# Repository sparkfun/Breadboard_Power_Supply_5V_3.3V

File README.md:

SparkFun Breadboard Power Supply 5V/3.3V
========================================

[*SparkFun Breadboard Power Supply 5V/3.3V (PRT-00114)*](https://www.sparkfun.com/products/114)

ere is a very simple breadboard power supply kit that takes power from a DC wall wart and outputs a selectable 5V or 3.3V regulated voltage.

Repository Contents
-------------------

* **/Hardware** - Eagle design files (.brd, .sch)
* **/Production** - Production panel files (.brd)

Documentation
--------------
* **[Hookup Guide](https://www.sparkfun.com/tutorials/297)** - Basic hookup guide for the Breadboard Power Supply.
* **[SparkFun Fritzing repo](https://github.com/sparkfun/Fritzing_Parts)** - Fritzing diagrams for SparkFun products.
* **[SparkFun 3D Model repo](https://github.com/sparkfun/3D_Models)** - 3D models of SparkFun products. 

License Information
-------------------
This product is _**open source**_! 

The **hardware** is released under [Creative Commons ShareAlike 4.0 International](https://creativecommons.org/licenses/by-sa/4.0/).

Please use, reuse, and modify these files as you see fit. Please maintain attribution to SparkFun Electronics and release anything derivative under the same license.

Distributed as-is; no warranty is given.

- Your friends at SparkFun.

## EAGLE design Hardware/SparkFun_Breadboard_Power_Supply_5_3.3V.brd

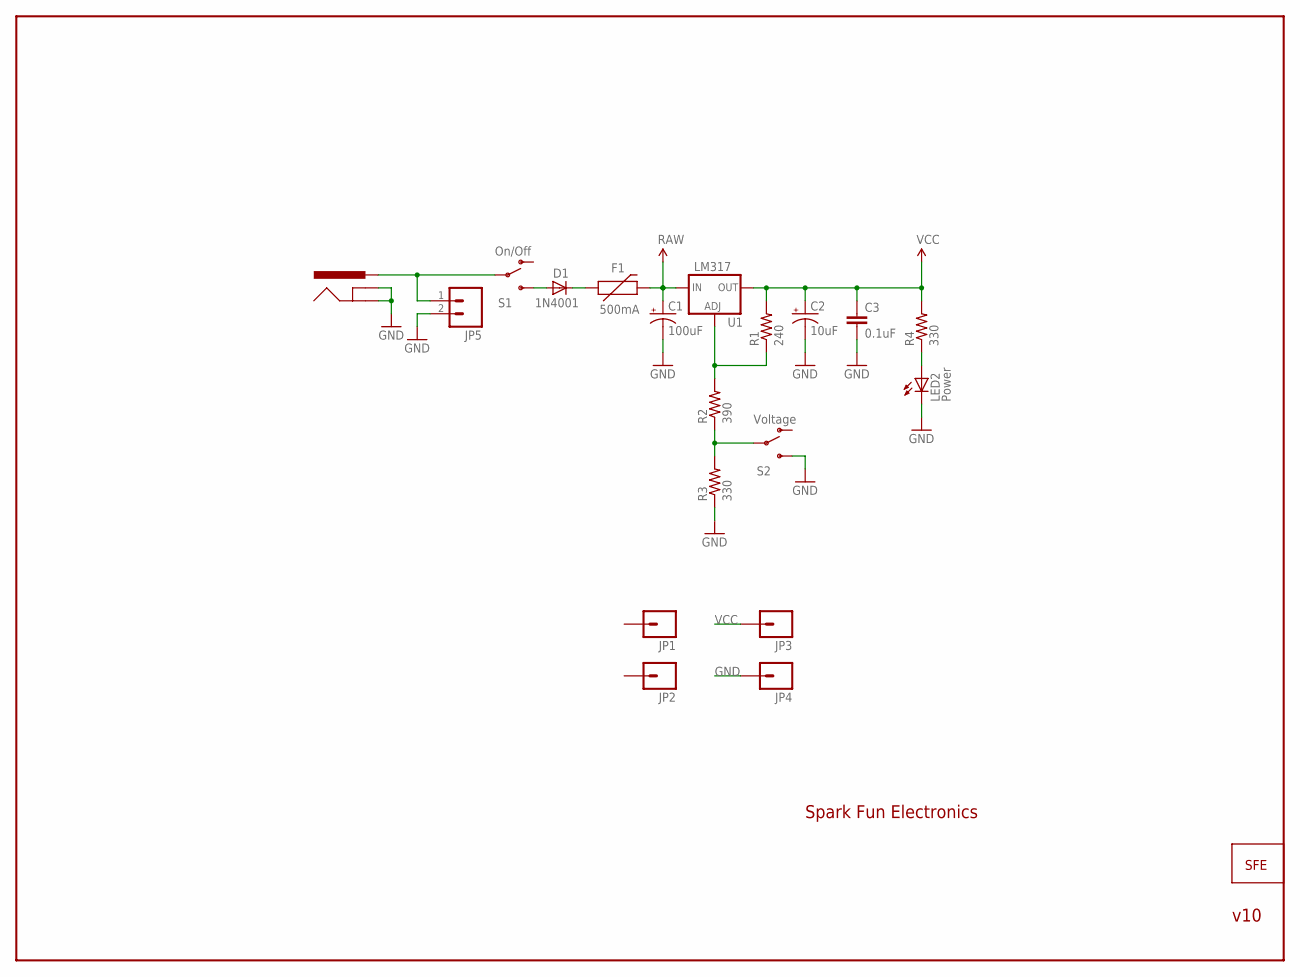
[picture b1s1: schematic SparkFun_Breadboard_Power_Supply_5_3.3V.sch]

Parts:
C1: 100uF; CPOL-RADIAL-100UF-25V
C2: 10uF; CPOL-RADIAL-10UF-25V
C3: 0.1uF; CAP-PTH-SMALL2
D1: 1N4001; DIODE-0.4
F1: 500mA; PTC
J1: POWER_JACKPTH; POWER_JACK_PTH
JP1, JP2, JP3, JP4: M01PTH; 1X01
JP5: M02PTH; 1X02
LED2: Power; LED5MM
R1: 240; AXIAL-0.3
R2: 390; AXIAL-0.3
R3, R4: 330; AXIAL-0.3
S1: On/Off; SWITCH-SPST
S2: Voltage; SWITCH-SPST
U1: LM317; TO220-ADJ
U$1: LOGO-SFESK; SFE-LOGO-FLAME

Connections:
GND: C1.2 (-), C2.2 (-), C3.2, J1.GND, J1.GNDBREAK, JP4.1, JP5.2, LED2.K (C), R3.P$1 (1), S2.3 (S)
unnamed: D1.C, F1.P$1 (1)
unnamed: D1.A, S1.3 (S)
unnamed: J1.PWR, JP5.1, S1.2
unnamed: R2.P$1 (1), R3.P$2 (2), S2.2
unnamed: R1.P$1 (1), R2.P$2 (2), U1.ADJ
unnamed: LED2.A, R4.P$1 (1)
RAW: C1.1 (+), F1.P$2 (2), U1.IN
VCC: C2.1 (+), C3.1, JP3.1, R1.P$2 (2), R4.P$2 (2), U1.OUT

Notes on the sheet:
Spark Fun Electronics
v10

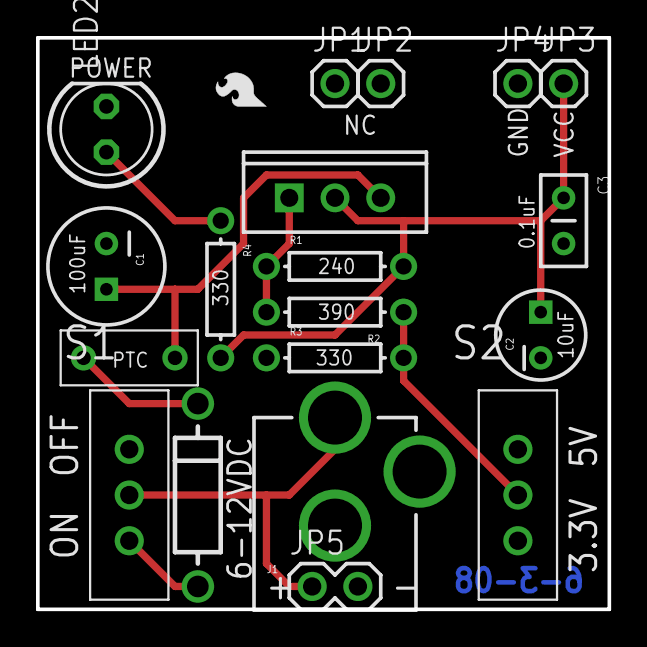
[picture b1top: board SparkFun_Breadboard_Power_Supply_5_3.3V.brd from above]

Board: 2 copper layers, 31.8 x 31.8 mm, 20 parts (0 on the bottom side), 9 nets.

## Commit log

2015-05-05 Adding hardware files, updating README
